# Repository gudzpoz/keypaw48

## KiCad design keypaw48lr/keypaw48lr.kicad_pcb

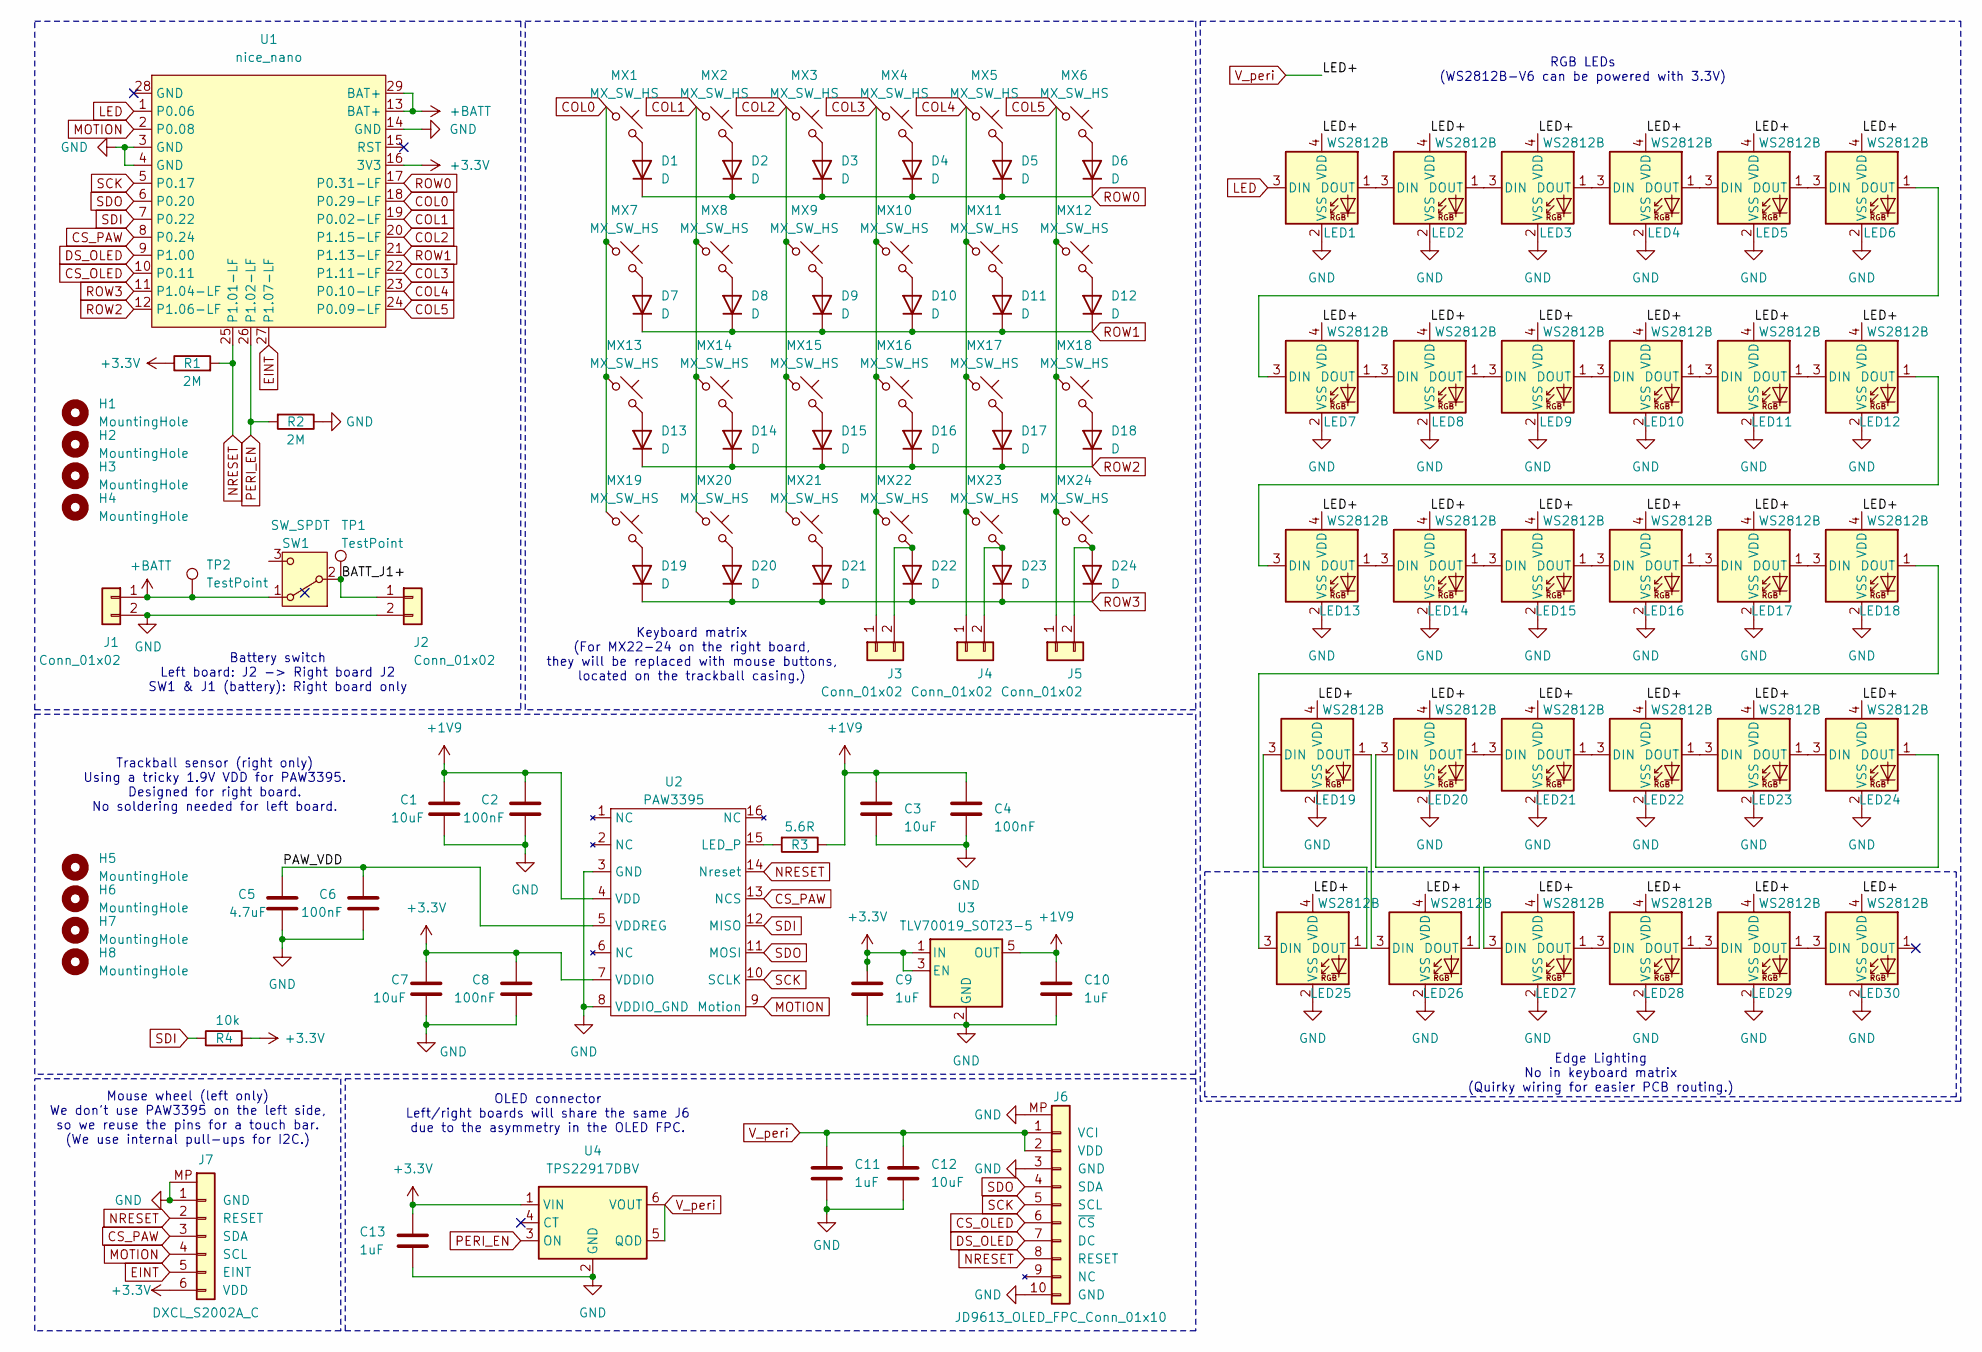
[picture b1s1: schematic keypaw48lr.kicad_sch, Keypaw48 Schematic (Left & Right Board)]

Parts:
C1, C3, C7, C12: 10uF; C_1206_3216Metric_Pad1.33x1.80mm_HandSolder
C2, C4, C6, C8: 100nF; C_0805_2012Metric_Pad1.18x1.45mm_HandSolder
C5: 4.7uF; C_1206_3216Metric_Pad1.33x1.80mm_HandSolder
C9, C10, C11: 1uF; C_1206_3216Metric_Pad1.33x1.80mm_HandSolder
C13: 1uF; C_1206_3216Metric_Pad1.33x1.80mm_HandSolder_REV
D1, D2, D3, D4, D5, D6, D7, D8, D9, D10, D11, D12, D13, D14, D15, D16, D17, D18, D19, D20, D21, D22, D23, D24: D; D_SOD-123_REV
H1, H2, H3, H4, H5, H6, H7, H8: MountingHole; MountingHole_2.2mm_M2_DIN965_Pad_TopBottom
J1: Conn_01x02; Conn_1x02_P1.25mm_Horizontal_Battery_REV
J2: Conn_01x02; Conn_1x02_P1.25mm_Horizontal_Battery
J3, J4, J5: Conn_01x02; Molex_PicoBlade_53048-0210_1x02_P1.25mm_Horizontal
J6: JD9613_OLED_FPC_Conn_01x10; FH34SRJ-10S-0.5SH
J7: DXCL_S2002A_C; FH34SRJ-10S-0.5SH
LED1, LED2, LED3, LED4, LED5, LED6, LED7, LED8, LED9, LED10, LED11, LED12, LED13, LED14, LED15, LED16, LED17, LED18, LED19, LED20, LED21, LED22, LED23, LED24, LED25, LED26, LED27, LED28, LED29, LED30: WS2812B; LED_WS2812B-2020_backmount_rev
MX1, MX2, MX3, MX4, MX5, MX6, MX7, MX8, MX9, MX10, MX11, MX12, MX13, MX14, MX15, MX16, MX17, MX18, MX19, MX20, MX21, MX22, MX23, MX24: MX_SW_HS; SW_MX_HS_REV
R1, R2: 2M; R_1206_3216Metric_Pad1.30x1.75mm_HandSolder
R3: 5.6R; R_1206_3216Metric_Pad1.30x1.75mm_HandSolder
R4: 10k; R_1206_3216Metric_Pad1.30x1.75mm_HandSolder
SW1: SW_SPDT; SW_SPDT_CK_JS102011SAQN
TP1, TP2: TestPoint; TestPoint_THTPad_D2.0mm_Drill1.0mm_nosilk
U1: nice_nano; nice_nano_AH_USBup_REV
U2: PAW3395
U3: TLV70019_SOT23-5; SOT-23-5_HandSoldering
U4: TPS22917DBV; SOT-23-6_Handsoldering_REV

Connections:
+1V9: C1.1, C2.1, C3.1, C4.1, C10.1, R3.1, U2.4 (VDD), U3.5 (OUT)
+3.3V: C7.1, C8.1, C9.1, C13.1, J7.6 (VDD), R1.1, R4.2, U1.16 (3V3), U2.7 (VDDIO), U3.1 (IN), U3.3 (EN), U4.1 (VIN)
+BATT: J1.1, SW1.1 (A), TP2.1 (1_1), U1.13 (BAT+), U1.29 (BAT+)
/BATT_J1+: J2.1, SW1.2 (B), TP1.1 (1_1)
/PAW_VDD: C5.1, C6.1, U2.5 (VDDREG)
COL0: MX1.1, MX7.1, MX13.1, MX19.1, U1.18 (P0.29-LF)
COL1: MX2.1, MX8.1, MX14.1, MX20.1, U1.19 (P0.02-LF)
COL2: MX3.1, MX9.1, MX15.1, MX21.1, U1.20 (P1.15-LF)
COL3: J3.1, MX4.1, MX10.1, MX16.1, MX22.1, U1.22 (P1.11-LF)
COL4: J4.1, MX5.1, MX11.1, MX17.1, MX23.1, U1.23 (P0.10-LF)
COL5: J5.1, MX6.1, MX12.1, MX18.1, MX24.1, U1.24 (P0.09-LF)
CS_OLED: J6.6 (~CS), U1.10 (P0.11)
CS_PAW: J7.3 (SDA), U1.8 (P0.24), U2.13 (NCS)
DS_OLED: J6.7 (DC), U1.9 (P1.00)
EINT: J7.5 (EINT), U1.27 (P1.07-LF)
GND: C1.2, C2.2, C3.2, C4.2, C5.2, C6.2, C7.2, C8.2, C9.2, C10.2, C11.2, C12.2, C13.2, J1.2, J2.2, J6.3 (GND), J6.10 (GND), J6.MP, J7.1 (GND), J7.MP, LED1.2 (VSS), LED2.2 (VSS), LED3.2 (VSS), LED4.2 (VSS), LED5.2 (VSS), LED6.2 (VSS), LED7.2 (VSS), LED8.2 (VSS), LED9.2 (VSS), LED10.2 (VSS), LED11.2 (VSS), LED12.2 (VSS), LED13.2 (VSS), LED14.2 (VSS), LED15.2 (VSS), LED16.2 (VSS), LED17.2 (VSS), LED18.2 (VSS), LED19.2 (VSS), LED20.2 (VSS), LED21.2 (VSS), LED22.2 (VSS), LED23.2 (VSS), LED24.2 (VSS), LED25.2 (VSS), LED26.2 (VSS), LED27.2 (VSS), LED28.2 (VSS), LED29.2 (VSS), LED30.2 (VSS), R2.1, U1.3 (GND), U1.4 (GND), U1.14 (GND), U2.3 (GND), U2.8 (VDDIO_GND), U3.2 (GND), U4.2 (GND)
LED: LED1.3 (DIN), U1.1 (P0.06)
MOTION: J7.4 (SCL), U1.2 (P0.08), U2.9 (Motion)
NRESET: J6.8 (RESET), J7.2 (RESET), R1.2, U1.25 (P1.01-LF), U2.14 (Nreset)
unnamed: D1.2 (A), MX1.2
unnamed: D2.2 (A), MX2.2
unnamed: D3.2 (A), MX3.2
unnamed: D4.2 (A), MX4.2
unnamed: D5.2 (A), MX5.2
unnamed: D6.2 (A), MX6.2
unnamed: D7.2 (A), MX7.2
unnamed: D8.2 (A), MX8.2
unnamed: D9.2 (A), MX9.2
unnamed: D10.2 (A), MX10.2
unnamed: D11.2 (A), MX11.2
unnamed: D12.2 (A), MX12.2
unnamed: D13.2 (A), MX13.2
unnamed: D14.2 (A), MX14.2
unnamed: D15.2 (A), MX15.2
unnamed: D16.2 (A), MX16.2
unnamed: D17.2 (A), MX17.2
unnamed: D18.2 (A), MX18.2
unnamed: D19.2 (A), MX19.2
unnamed: D20.2 (A), MX20.2
unnamed: D21.2 (A), MX21.2
unnamed: D22.2 (A), J3.2, MX22.2
unnamed: D23.2 (A), J4.2, MX23.2
unnamed: D24.2 (A), J5.2, MX24.2
unnamed: LED1.1 (DOUT), LED2.3 (DIN)
unnamed: LED2.1 (DOUT), LED3.3 (DIN)
unnamed: LED3.1 (DOUT), LED4.3 (DIN)
unnamed: LED4.1 (DOUT), LED5.3 (DIN)
unnamed: LED5.1 (DOUT), LED6.3 (DIN)
unnamed: LED6.1 (DOUT), LED7.3 (DIN)
unnamed: LED7.1 (DOUT), LED8.3 (DIN)
unnamed: LED8.1 (DOUT), LED9.3 (DIN)
unnamed: LED9.1 (DOUT), LED10.3 (DIN)
unnamed: LED10.1 (DOUT), LED11.3 (DIN)
unnamed: LED11.1 (DOUT), LED12.3 (DIN)
unnamed: LED12.1 (DOUT), LED13.3 (DIN)
unnamed: LED13.1 (DOUT), LED14.3 (DIN)
unnamed: LED14.1 (DOUT), LED15.3 (DIN)
unnamed: LED15.1 (DOUT), LED16.3 (DIN)
unnamed: LED16.1 (DOUT), LED17.3 (DIN)
unnamed: LED17.1 (DOUT), LED18.3 (DIN)
unnamed: LED18.1 (DOUT), LED25.3 (DIN)
unnamed: LED19.3 (DIN), LED25.1 (DOUT)
unnamed: LED19.1 (DOUT), LED26.3 (DIN)
unnamed: LED20.3 (DIN), LED26.1 (DOUT)
unnamed: LED20.1 (DOUT), LED21.3 (DIN)
unnamed: LED21.1 (DOUT), LED22.3 (DIN)
unnamed: LED22.1 (DOUT), LED23.3 (DIN)
unnamed: LED23.1 (DOUT), LED24.3 (DIN)
unnamed: LED24.1 (DOUT), LED27.3 (DIN)
unnamed: LED27.1 (DOUT), LED28.3 (DIN)
unnamed: LED28.1 (DOUT), LED29.3 (DIN)
unnamed: LED29.1 (DOUT), LED30.3 (DIN)
unnamed: R3.2, U2.15 (LED_P)
PERI_EN: R2.2, U1.26 (P1.02-LF), U4.3 (ON)
ROW0: D1.1 (K), D2.1 (K), D3.1 (K), D4.1 (K), D5.1 (K), D6.1 (K), U1.17 (P0.31-LF)
ROW1: D7.1 (K), D8.1 (K), D9.1 (K), D10.1 (K), D11.1 (K), D12.1 (K), U1.21 (P1.13-LF)
ROW2: D13.1 (K), D14.1 (K), D15.1 (K), D16.1 (K), D17.1 (K), D18.1 (K), U1.12 (P1.06-LF)
ROW3: D19.1 (K), D20.1 (K), D21.1 (K), D22.1 (K), D23.1 (K), D24.1 (K), U1.11 (P1.04-LF)
SCK: J6.5 (SCL), U1.5 (P0.17), U2.10 (SCLK)
SDI: R4.1, U1.7 (P0.22), U2.12 (MISO)
SDO: J6.4 (SDA), U1.6 (P0.20), U2.11 (MOSI)
V_peri: C11.1, C12.1, J6.1 (VCI), J6.2 (VDD), LED1.4 (VDD), LED2.4 (VDD), LED3.4 (VDD), LED4.4 (VDD), LED5.4 (VDD), LED6.4 (VDD), LED7.4 (VDD), LED8.4 (VDD), LED9.4 (VDD), LED10.4 (VDD), LED11.4 (VDD), LED12.4 (VDD), LED13.4 (VDD), LED14.4 (VDD), LED15.4 (VDD), LED16.4 (VDD), LED17.4 (VDD), LED18.4 (VDD), LED19.4 (VDD), LED20.4 (VDD), LED21.4 (VDD), LED22.4 (VDD), LED23.4 (VDD), LED24.4 (VDD), LED25.4 (VDD), LED26.4 (VDD), LED27.4 (VDD), LED28.4 (VDD), LED29.4 (VDD), LED30.4 (VDD), U4.5 (QOD), U4.6 (VOUT)

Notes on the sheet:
Trackball sensor (right only) Using a tricky 1.9V VDD for PAW3395. Designed for right board. No soldering needed for left board.
Battery switch Left board: J2 -> Right board J2 SW1 & J1 (battery): Right board only
Mouse wheel (left only) We don't use PAW3395 on the left side, so we reuse the pins for a touch bar. (We use internal pull-ups for I2C.)
Edge Lighting No in keyboard matrix (Quirky wiring for easier PCB routing.)
OLED connector Left/right boards will share the same J6 due to the asymmetry in the OLED FPC.
Keyboard matrix (For MX22-24 on the right board, they will be replaced with mouse buttons, located on the trackball casing.)
RGB LEDs (WS2812B-V6 can be powered with 3.3V)

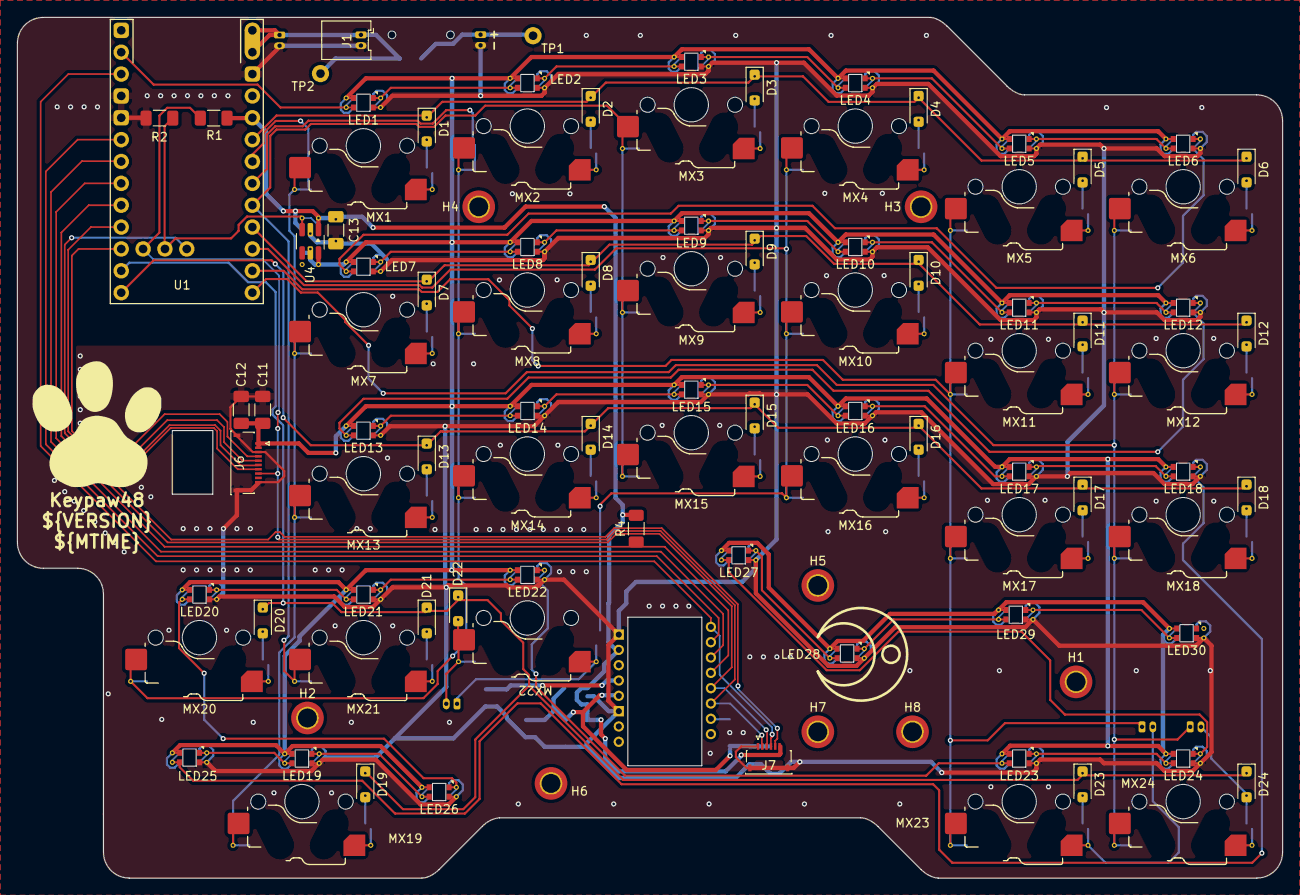
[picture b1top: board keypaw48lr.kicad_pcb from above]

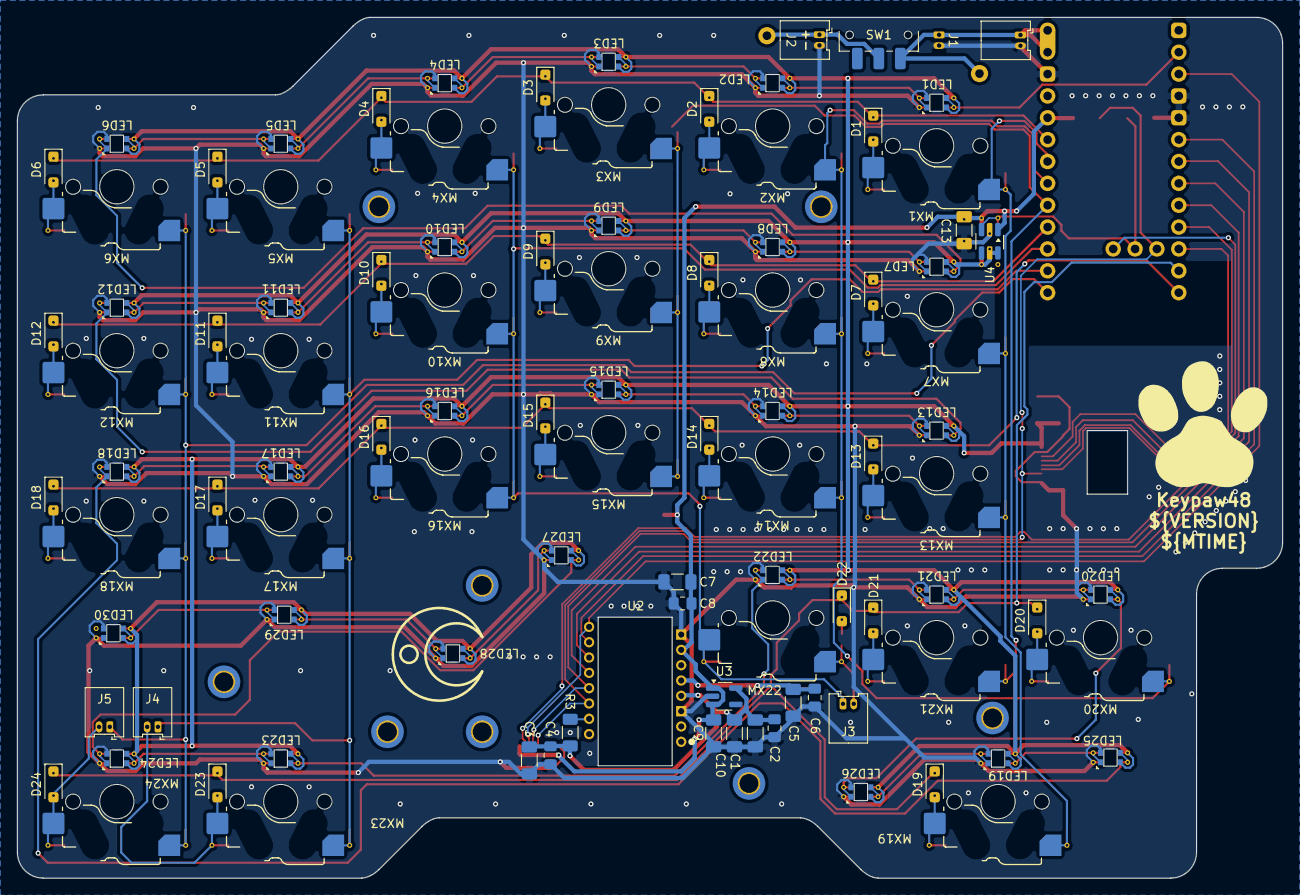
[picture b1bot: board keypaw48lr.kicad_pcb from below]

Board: 2 copper layers, 147.0 x 100.0 mm, 117 parts (21 on the bottom side), 82 nets.
